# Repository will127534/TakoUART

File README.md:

# TakoUART - 8ch USB to UART board

This 5cm x 5cm 4-layer board is based on [CH348Q](http://www.wch-ic.com/products/CH348.html?) USB to 8 UART IC, I've also added level shifter (NTS0302JKZ) along with a overcurrent protector(NCP380) for user selectable 3.3V output on each UART port.

The board is designed with Kicad 6.0:

#inaART

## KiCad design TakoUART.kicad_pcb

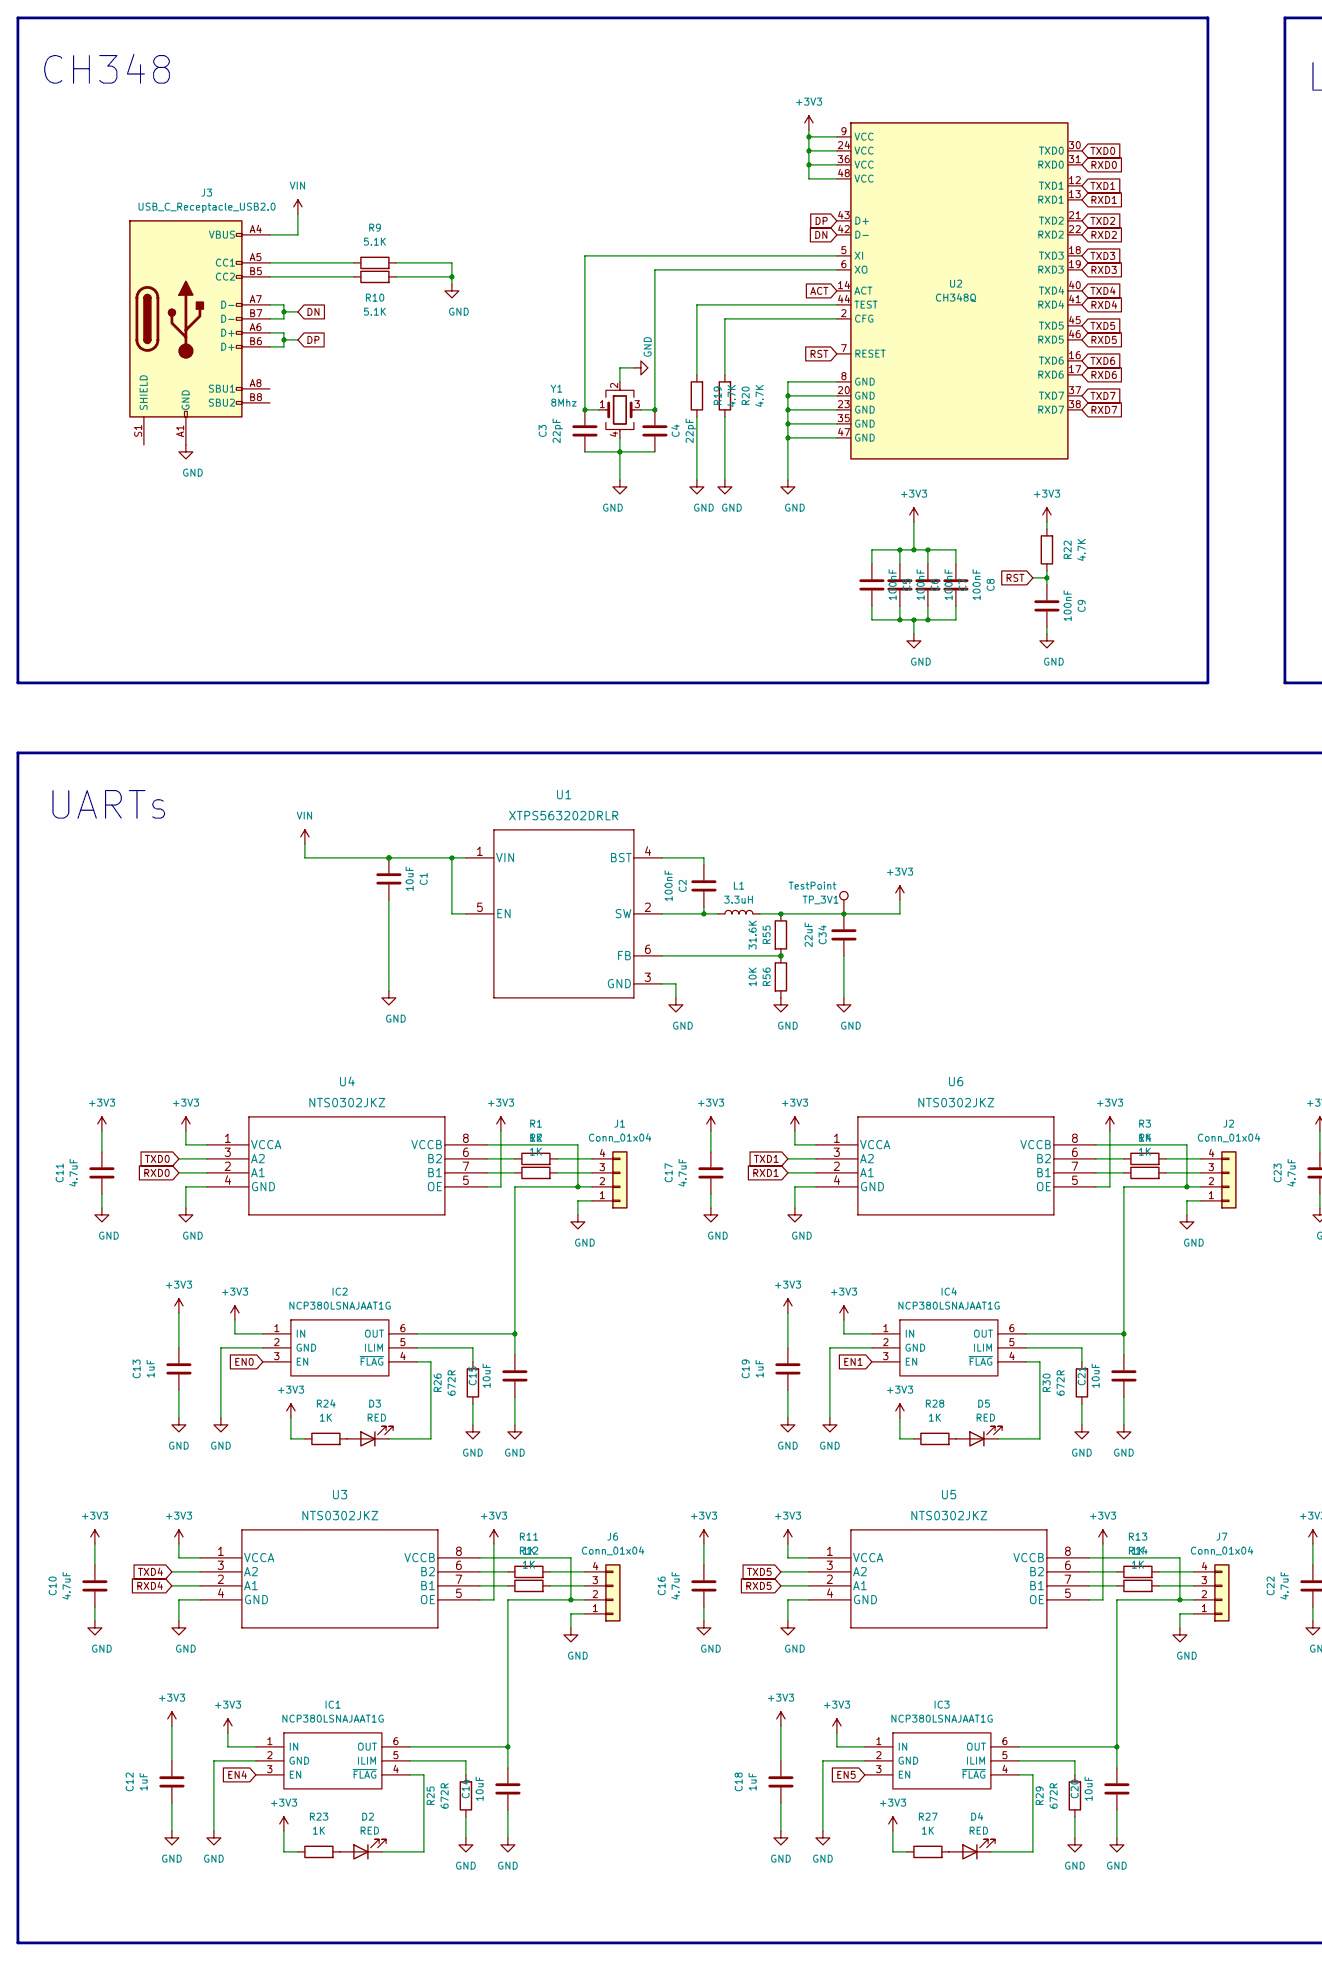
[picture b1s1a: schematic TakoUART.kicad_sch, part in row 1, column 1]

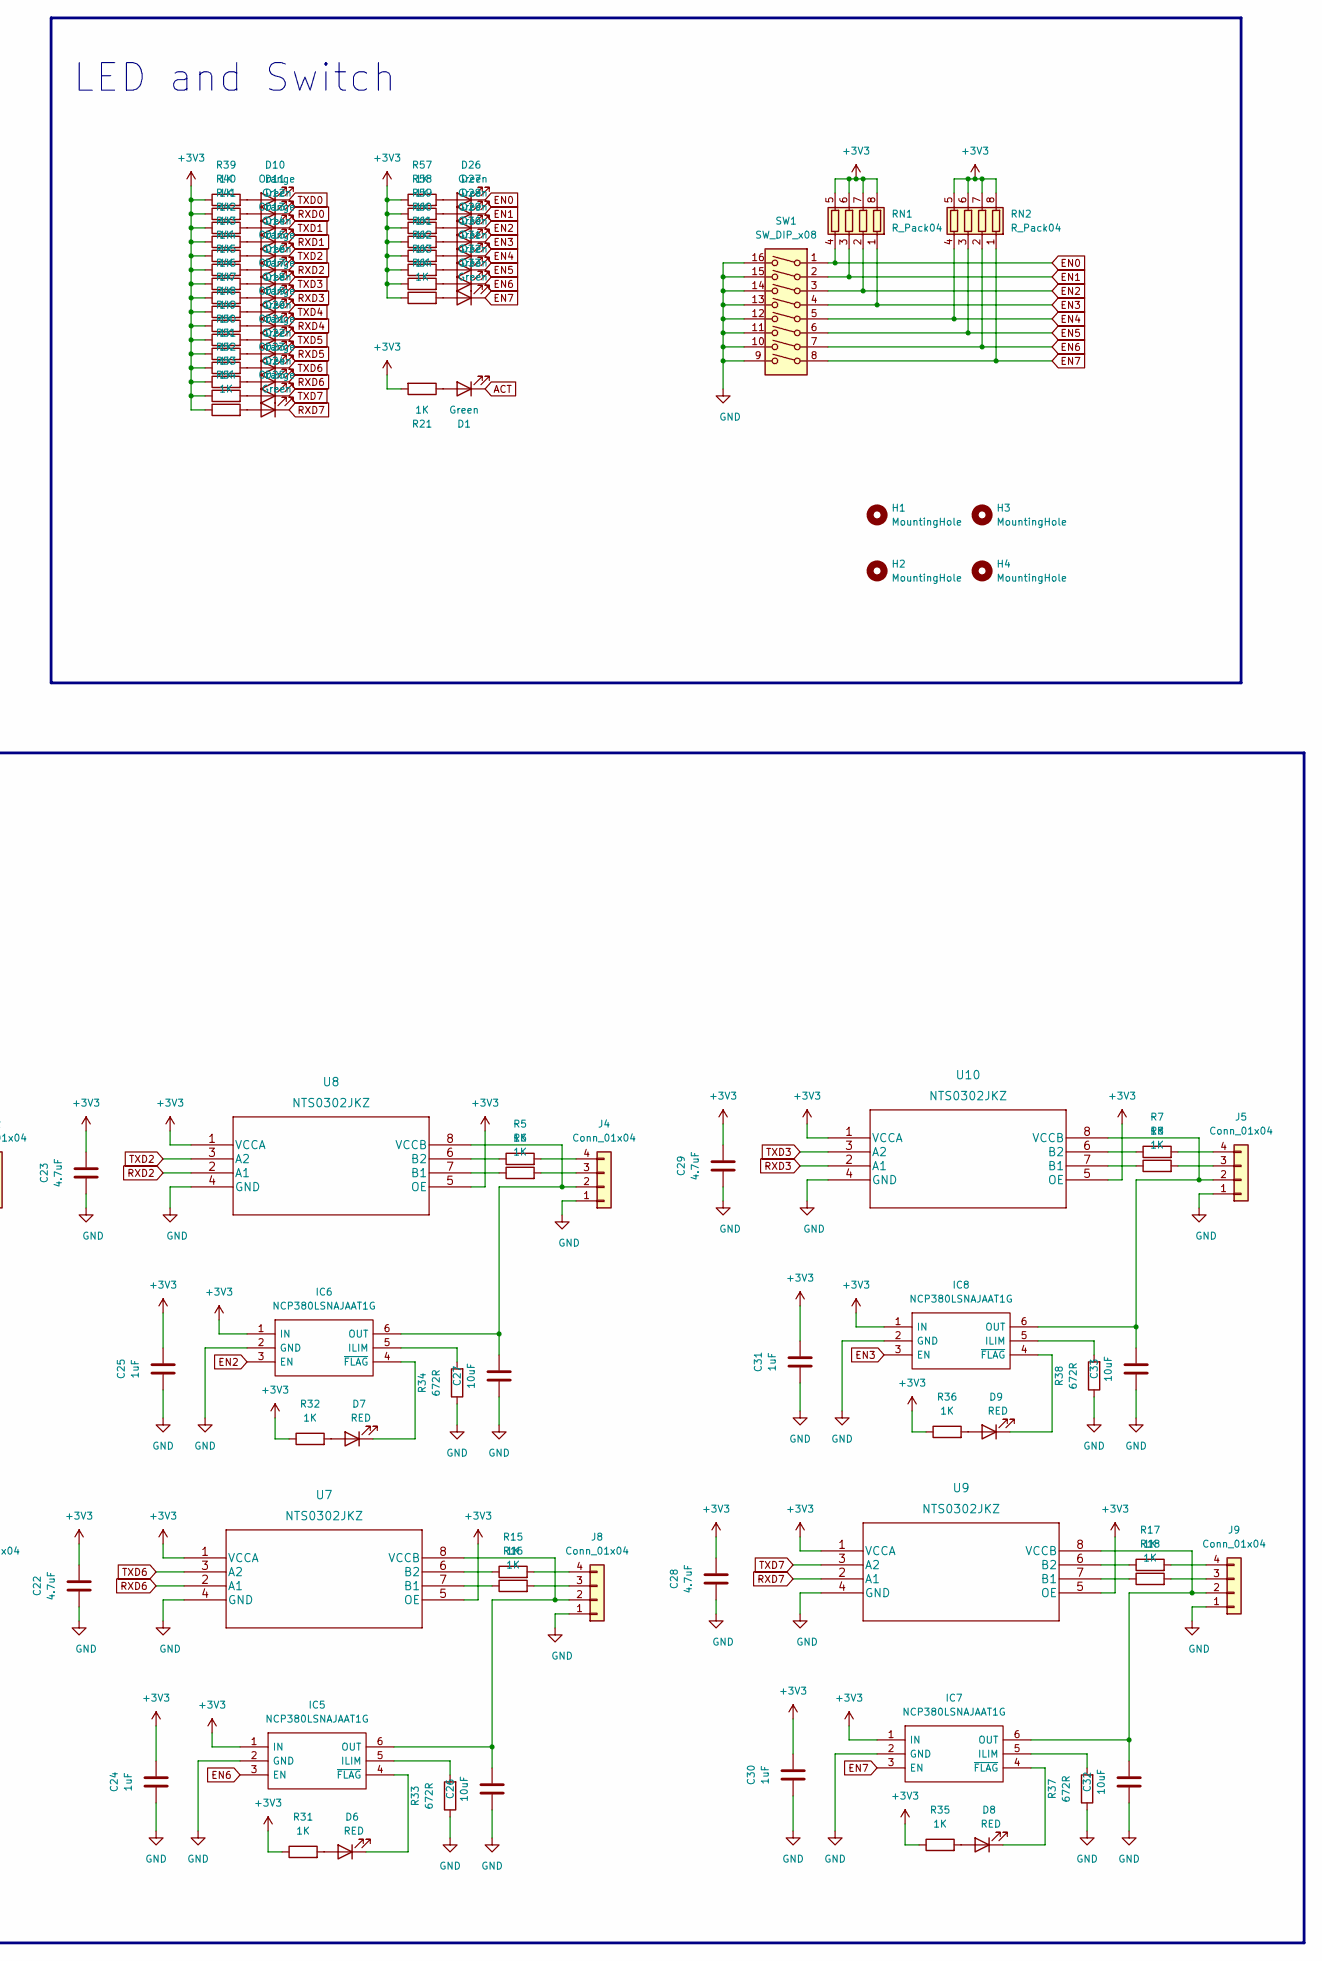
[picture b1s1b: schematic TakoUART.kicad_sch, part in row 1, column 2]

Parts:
C1: 10uF; C_0805_2012Metric
C2, C5, C6, C7, C8, C9: 100nF; C_0402_1005Metric
C3, C4: 22pF; C_0402_1005Metric
C10, C11, C16, C17, C22, C23, C28, C29: 4.7uF; C_0402_1005Metric
C12, C13, C18, C19, C24, C25, C30, C31: 1uF; C_0402_1005Metric
C14, C15, C20, C21, C26, C27, C32, C33: 10uF; C_0402_1005Metric
C34: 22uF; C_0805_2012Metric
D1, D11, D13, D15, D17, D19, D21, D23, D25, D26, D27, D28, D29, D30, D31, D32, D33: Green; LED_0402_1005Metric
D2, D3, D4, D5, D6, D7, D8, D9: RED; LED_0402_1005Metric
D10, D12, D14, D16, D18, D20, D22, D24: Orange; LED_0402_1005Metric
H1, H2, H3, H4: MountingHole; MountingHole_3.2mm_M3
IC1, IC2, IC3, IC4, IC5, IC6, IC7, IC8: NCP380LSNAJAAT1G; SOT95P275X110-6N; Mouser Part Number 863-NCP380LSNAJAAT1G
J1, J2, J4, J5, J6, J7, J8, J9: Conn_01x04; JST_SH_BM04B-SRSS-TB_1x04-1MP_P1.00mm_Vertical
J3: USB_C_Receptacle_USB2.0; USB_C_Receptacle_XKB_U262-16XN-4BVC11
L1: 3.3uH; L_Vishay_IHLP-1212
R1, R2, R3, R4, R5, R6, R7, R8, R11, R12, R13, R14, R15, R16, R17, R18, R21, R23, R24, R27, R28, R31, R32, R35, R36, R39, R40, R41, R42, R43, R44, R45, R46, R47, R48, R49, R50, R51, R52, R53, R54, R57, R58, R59, R60, R61, R62, R63, R64: 1K; R_0402_1005Metric
R9, R10: 5.1K; R_0402_1005Metric
R19, R20, R22: 4.7K; R_0402_1005Metric
R25, R26, R29, R30, R33, R34, R37, R38: 672R; R_0402_1005Metric
R55: 31.6K; R_0402_1005Metric
R56: 10K; R_0402_1005Metric
RN1, RN2: R_Pack04; R_Array_Concave_4x0603
SW1: SW_DIP_x08; SW_DIP_SPSTx08_Slide_6.7x21.88mm_W8.61mm_P2.54mm_LowProfile
TP_3V1: TestPoint; TestPoint_Pad_D1.0mm
U1: XTPS563202DRLR
U2: CH348Q; LQFP-48_7x7mm_P0.5mm
U3, U4, U5, U6, U7, U8, U9, U10: NTS0302JKZ
Y1: 8Mhz; Crystal_SMD_3225-4Pin_3.2x2.5mm

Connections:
+3V3: C5.1, C6.1, C7.1, C8.1, C10.2, C11.2, C12.2, C13.2, C16.2, C17.2, C18.2, C19.2, C22.2, C23.2, C24.2, C25.2, C28.2, C29.2, C30.2, C31.2, C34.1, IC1.1 (IN), IC2.1 (IN), IC3.1 (IN), IC4.1 (IN), IC5.1 (IN), IC6.1 (IN), IC7.1 (IN), IC8.1 (IN), L1.2, R21.2, R22.2, R23.1, R24.1, R27.1, R28.1, R31.1, R32.1, R35.1, R36.1, R39.1, R40.1, R41.1, R42.1, R43.1, R44.1, R45.1, R46.1, R47.1, R48.1, R49.1, R50.1, R51.1, R52.1, R53.1, R54.1, R55.1, R57.1, R58.1, R59.1, R60.1, R61.1, R62.1, R63.1, R64.1, RN1.5 (R4.2), RN1.6 (R3.2), RN1.7 (R2.2), RN1.8 (R1.2), RN2.5 (R4.2), RN2.6 (R3.2), RN2.7 (R2.2), RN2.8 (R1.2), TP_3V1.1, U2.9 (VCC), U2.24 (VCC), U2.36 (VCC), U2.48 (VCC), U3.1 (VCCA), U3.5 (OE), U4.1 (VCCA), U4.5 (OE), U5.1 (VCCA), U5.5 (OE), U6.1 (VCCA), U6.5 (OE), U7.1 (VCCA), U7.5 (OE), U8.1 (VCCA), U8.5 (OE), U9.1 (VCCA), U9.5 (OE), U10.1 (VCCA), U10.5 (OE)
ACT: D1.1 (K), U2.14 (ACT)
DN: J3.A7 (D-), J3.B7 (D-), U2.42 (D-)
DP: J3.A6 (D+), J3.B6 (D+), U2.43 (D+)
EN0: D26.1 (K), IC2.3 (EN), RN1.4 (R4.1), SW1.1
EN1: D27.1 (K), IC4.3 (EN), RN1.3 (R3.1), SW1.2
EN2: D28.1 (K), IC6.3 (EN), RN1.2 (R2.1), SW1.3
EN3: D29.1 (K), IC8.3 (EN), RN1.1 (R1.1), SW1.4
EN4: D30.1 (K), IC1.3 (EN), RN2.4 (R4.1), SW1.5
EN5: D31.1 (K), IC3.3 (EN), RN2.3 (R3.1), SW1.6
EN6: D32.1 (K), IC5.3 (EN), RN2.2 (R2.1), SW1.7
EN7: D33.1 (K), IC7.3 (EN), RN2.1 (R1.1), SW1.8
GND: C1.2, C3.1, C4.1, C5.2, C6.2, C7.2, C8.2, C9.2, C10.1, C11.1, C12.1, C13.1, C14.1, C15.1, C16.1, C17.1, C18.1, C19.1, C20.1, C21.1, C22.1, C23.1, C24.1, C25.1, C26.1, C27.1, C28.1, C29.1, C30.1, C31.1, C32.1, C33.1, C34.2, IC1.2 (GND), IC2.2 (GND), IC3.2 (GND), IC4.2 (GND), IC5.2 (GND), IC6.2 (GND), IC7.2 (GND), IC8.2 (GND), J1.1, J2.1, J3.A1 (GND), J3.A12 (GND), J3.B1 (GND), J3.B12 (GND), J4.1, J5.1, J6.1, J7.1, J8.1, J9.1, R9.2, R10.2, R19.1, R20.1, R25.1, R26.1, R29.1, R30.1, R33.1, R34.1, R37.1, R38.1, R56.2, SW1.9, SW1.10, SW1.11, SW1.12, SW1.13, SW1.14, SW1.15, SW1.16, U1.3 (GND), U2.8 (GND), U2.20 (GND), U2.23 (GND), U2.35 (GND), U2.47 (GND), U3.4 (GND), U4.4 (GND), U5.4 (GND), U6.4 (GND), U7.4 (GND), U8.4 (GND), U9.4 (GND), U10.4 (GND), Y1.2, Y1.4
unnamed: C2.1, U1.4 (BST)
unnamed: C2.2, L1.1, U1.2 (SW)
unnamed: C3.2, U2.5 (XI), Y1.1
unnamed: C4.2, U2.6 (XO), Y1.3
unnamed: C14.2, IC1.6 (OUT), J6.2, U3.8 (VCCB)
unnamed: C15.2, IC2.6 (OUT), J1.2, U4.8 (VCCB)
unnamed: C20.2, IC3.6 (OUT), J7.2, U5.8 (VCCB)
unnamed: C21.2, IC4.6 (OUT), J2.2, U6.8 (VCCB)
unnamed: C26.2, IC5.6 (OUT), J8.2, U7.8 (VCCB)
unnamed: C27.2, IC6.6 (OUT), J4.2, U8.8 (VCCB)
unnamed: C32.2, IC7.6 (OUT), J9.2, U9.8 (VCCB)
unnamed: C33.2, IC8.6 (OUT), J5.2, U10.8 (VCCB)
unnamed: D1.2 (A), R21.1
unnamed: D2.1 (K), IC1.4 (~FLAG)
unnamed: D2.2 (A), R23.2
unnamed: D3.1 (K), IC2.4 (~FLAG)
unnamed: D3.2 (A), R24.2
unnamed: D4.1 (K), IC3.4 (~FLAG)
unnamed: D4.2 (A), R27.2
unnamed: D5.1 (K), IC4.4 (~FLAG)
unnamed: D5.2 (A), R28.2
unnamed: D6.1 (K), IC5.4 (~FLAG)
unnamed: D6.2 (A), R31.2
unnamed: D7.1 (K), IC6.4 (~FLAG)
unnamed: D7.2 (A), R32.2
unnamed: D8.1 (K), IC7.4 (~FLAG)
unnamed: D8.2 (A), R35.2
unnamed: D9.1 (K), IC8.4 (~FLAG)
unnamed: D9.2 (A), R36.2
unnamed: D10.2 (A), R39.2
unnamed: D11.2 (A), R40.2
unnamed: D12.2 (A), R41.2
unnamed: D13.2 (A), R42.2
unnamed: D14.2 (A), R43.2
unnamed: D15.2 (A), R44.2
unnamed: D16.2 (A), R45.2
unnamed: D17.2 (A), R46.2
unnamed: D18.2 (A), R47.2
unnamed: D19.2 (A), R48.2
unnamed: D20.2 (A), R49.2
unnamed: D21.2 (A), R50.2
unnamed: D22.2 (A), R51.2
unnamed: D23.2 (A), R52.2
unnamed: D24.2 (A), R53.2
unnamed: D25.2 (A), R54.2
unnamed: D26.2 (A), R57.2
unnamed: D27.2 (A), R58.2
unnamed: D28.2 (A), R59.2
unnamed: D29.2 (A), R60.2
unnamed: D30.2 (A), R61.2
unnamed: D31.2 (A), R62.2
unnamed: D32.2 (A), R63.2
unnamed: D33.2 (A), R64.2
unnamed: IC1.5 (ILIM), R25.2
unnamed: IC2.5 (ILIM), R26.2
unnamed: IC3.5 (ILIM), R29.2
unnamed: IC4.5 (ILIM), R30.2
unnamed: IC5.5 (ILIM), R33.2
unnamed: IC6.5 (ILIM), R34.2
unnamed: IC7.5 (ILIM), R37.2
unnamed: IC8.5 (ILIM), R38.2
unnamed: J1.3, R2.2
unnamed: J1.4, R1.2
unnamed: J2.3, R4.2
unnamed: J2.4, R3.2
unnamed: J3.A5 (CC1), R9.1
unnamed: J3.B5 (CC2), R10.1
unnamed: J4.3, R6.2
unnamed: J4.4, R5.2
unnamed: J5.3, R8.2
unnamed: J5.4, R7.2
unnamed: J6.3, R12.2
unnamed: J6.4, R11.2
unnamed: J7.3, R14.2
unnamed: J7.4, R13.2
unnamed: J8.3, R16.2
unnamed: J8.4, R15.2
unnamed: J9.3, R18.2
unnamed: J9.4, R17.2
unnamed: R1.1, U4.6 (B2)
unnamed: R2.1, U4.7 (B1)
unnamed: R3.1, U6.6 (B2)
unnamed: R4.1, U6.7 (B1)
unnamed: R5.1, U8.6 (B2)
unnamed: R6.1, U8.7 (B1)
unnamed: R7.1, U10.6 (B2)
unnamed: R8.1, U10.7 (B1)
unnamed: R11.1, U3.6 (B2)
unnamed: R12.1, U3.7 (B1)
unnamed: R13.1, U5.6 (B2)
unnamed: R14.1, U5.7 (B1)
unnamed: R15.1, U7.6 (B2)
unnamed: R16.1, U7.7 (B1)
unnamed: R17.1, U9.6 (B2)
unnamed: R18.1, U9.7 (B1)
unnamed: R19.2, U2.44 (TEST)
unnamed: R20.2, U2.2 (CFG)
unnamed: R55.2, R56.1, U1.6 (FB)
RST: C9.1, R22.1, U2.7 (RESET)
RXD0: D11.1 (K), U2.31 (RXD0), U4.2 (A1)
RXD1: D13.1 (K), U2.13 (RXD1), U6.2 (A1)
RXD2: D15.1 (K), U2.22 (RXD2), U8.2 (A1)
RXD3: D17.1 (K), U2.19 (RXD3), U10.2 (A1)
RXD4: D19.1 (K), U2.41 (RXD4), U3.2 (A1)
RXD5: D21.1 (K), U2.46 (RXD5), U5.2 (A1)
RXD6: D23.1 (K), U2.17 (RXD6), U7.2 (A1)
RXD7: D25.1 (K), U2.38 (RXD7), U9.2 (A1)
TXD0: D10.1 (K), U2.30 (TXD0), U4.3 (A2)
TXD1: D12.1 (K), U2.12 (TXD1), U6.3 (A2)
TXD2: D14.1 (K), U2.21 (TXD2), U8.3 (A2)
TXD3: D16.1 (K), U2.18 (TXD3), U10.3 (A2)
TXD4: D18.1 (K), U2.40 (TXD4), U3.3 (A2)
TXD5: D20.1 (K), U2.45 (TXD5), U5.3 (A2)
TXD6: D22.1 (K), U2.16 (TXD6), U7.3 (A2)
TXD7: D24.1 (K), U2.37 (TXD7), U9.3 (A2)
VIN: C1.1, J3.A4 (VBUS), J3.A9 (VBUS), J3.B4 (VBUS), J3.B9 (VBUS), U1.1 (VIN), U1.5 (EN)

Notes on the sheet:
UARTs
CH348
LED and Switch

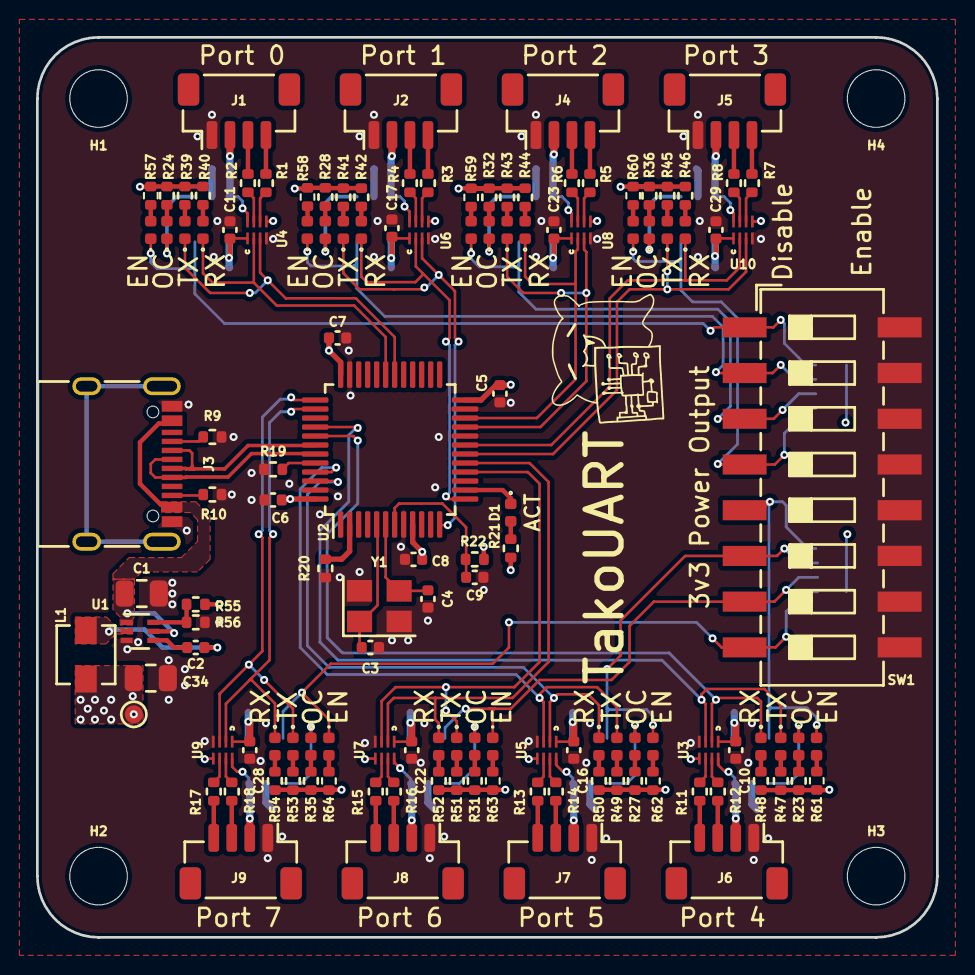
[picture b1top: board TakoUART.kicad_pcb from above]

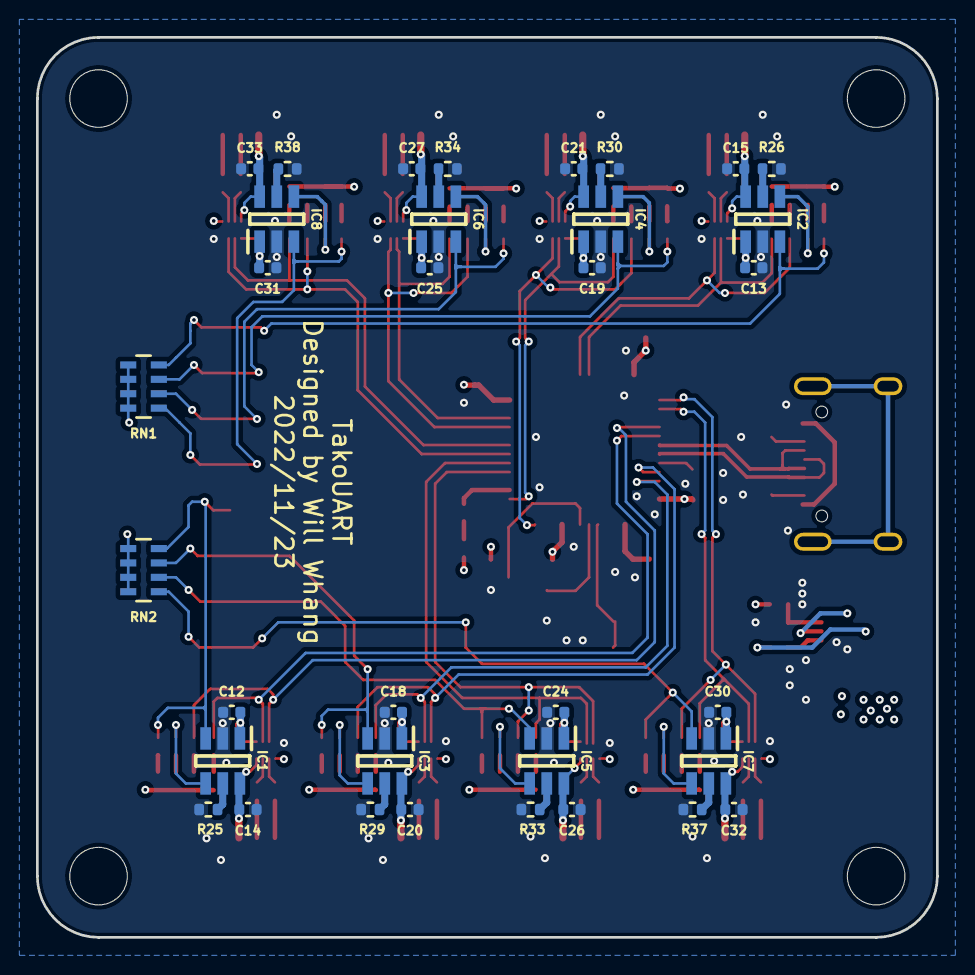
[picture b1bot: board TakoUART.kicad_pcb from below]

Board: 4 copper layers, 50.0 x 50.0 mm, 168 parts (34 on the bottom side), 129 nets.

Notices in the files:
parts and their libraries:
Copyright 2021 Accelerated Designs. All rights reserved.
